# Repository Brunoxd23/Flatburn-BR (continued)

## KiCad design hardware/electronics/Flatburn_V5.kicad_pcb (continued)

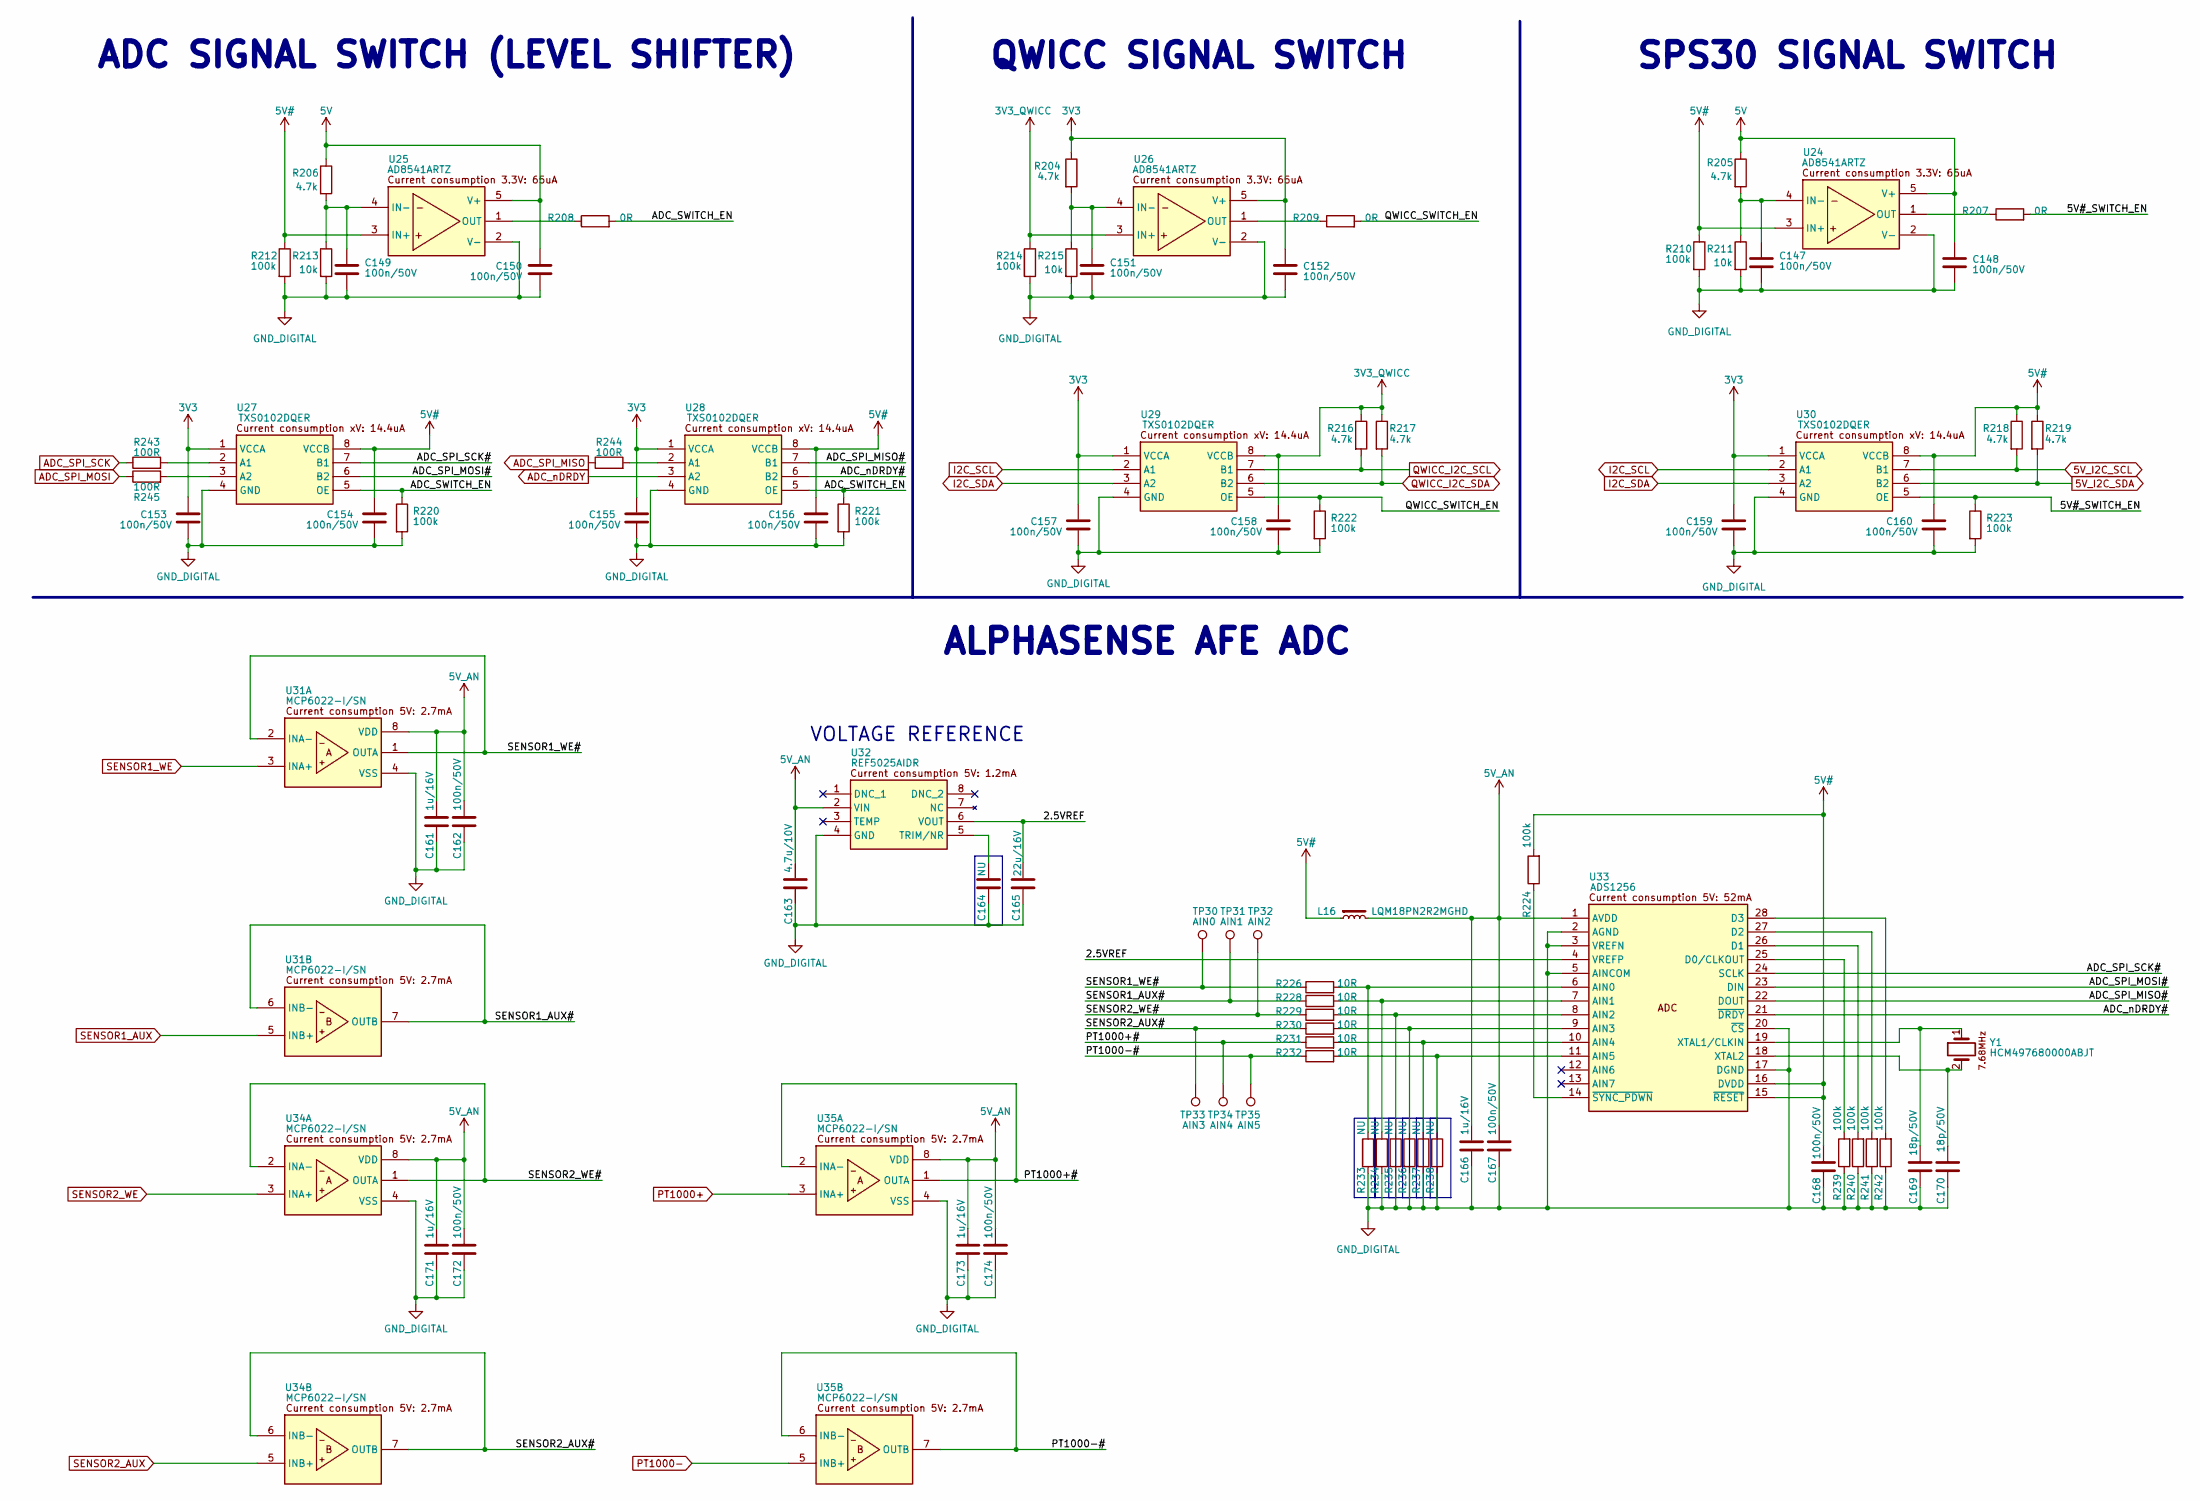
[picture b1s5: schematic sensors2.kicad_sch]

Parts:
C147, C148, C149, C150, C151, C152, C153, C154, C155, C156, C157, C158, C159, C160, C162, C167, C168, C172, C174: 100n/50V; C_0402_1005Metric
C161, C166, C171, C173: 1u/16V; C_0402_1005Metric; MPN GRM155C71C105KE11D
C163: 4.7u/10V; C_0603_1608Metric
C164: NU; C_0603_1608Metric; MPN CL10B105KA8NNNC
C165: 22u/16V; C_0603_1608Metric; MPN KGM15CR51C226MT
C169, C170: 18p/50V; C_0603_1608Metric; MPN C0603C180J5GAC7411
L16: LQM18PN2R2MGHD; L_0603_1608Metric; MPN LQM18PN2R2MGHD
R204, R205, R206, R216, R217, R218, R219: 4.7k; R_0402_1005Metric
R207, R208, R209: 0R; R_0402_1005Metric; MPN RCS04020000Z0ED
R210, R212, R214, R220, R221, R222, R223, R224, R239, R240, R241, R242: 100k; R_0402_1005Metric
R211, R213, R215: 10k; R_0402_1005Metric
R226, R228, R229, R230, R231, R232: 10R; R_0402_1005Metric; MPN RE0402DRE0710RL
R233, R234, R235, R236, R237, R238: NU; R_0402_1005Metric
R243, R244, R245: 100R; R_0402_1005Metric
TP30: AIN0; TestPoint_Pad_D1.0mm
TP31: AIN1; TestPoint_Pad_D1.0mm
TP32: AIN2; TestPoint_Pad_D1.0mm
TP33: AIN3; TestPoint_Pad_D1.0mm
TP34: AIN4; TestPoint_Pad_D1.0mm
TP35: AIN5; TestPoint_Pad_D1.0mm
U24, U25, U26: AD8541ARTZ; SOT-23-5; MPN TXS0102DQER
U27, U28, U29, U30: TXS0102DQER; SON35P100X140X40-8N; MPN TXS0102DQER
U31, U34, U35: MCP6022-I/SN; SOIC127P600X175-8N; MPN MCP6022-I/SN
U32: REF5025AIDR; SOIC127P600X175-8N; MPN REF5025AIDR
U33: ADS1256; DB28-M; MPN ADS1256IDBR
Y1: HCM497680000ABJT; MPN HCM497680000ABJT

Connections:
3V3: C152.1, C153.1, C155.1, C157.1, C159.1, R204.1, U26.5 (V+), U27.1 (VCCA), U28.1 (VCCA), U29.1 (VCCA), U30.1 (VCCA); also elsewhere on the board
3V3_QWICC: C158.1, R214.1, R216.1, R217.1, U26.3 (IN+), U29.8 (VCCB); also elsewhere on the board
5V: C148.1, C150.1, R205.1, R206.1, U24.5 (V+), U25.5 (V+); also elsewhere on the board
5V#: C154.1, C156.1, C160.1, C168.1, L16.2, R210.1, R212.1, R218.1, R219.1, R224.2, U24.3 (IN+), U25.3 (IN+), U27.8 (VCCB), U28.8 (VCCB), U30.8 (VCCB), U33.15 (~RESET), U33.16 (DVDD); also elsewhere on the board
5V_AN: C161.1, C162.1, C163.1, C166.1, C167.1, C171.1, C172.1, C173.1, C174.1, L16.1, U31.8 (VDD), U32.2 (VIN), U33.1 (AVDD), U34.8 (VDD), U35.8 (VDD)
5V_I2C_SCL: R218.2, U30.7 (B1); also elsewhere on the board
5V_I2C_SDA: R219.2, U30.6 (B2); also elsewhere on the board
/08 - SENSORS 2/2.5VREF: C165.1, U32.6 (VOUT), U33.4 (VREFP)
/08 - SENSORS 2/5V#_SWITCH_EN: R207.2, R223.1, U30.5 (OE)
/08 - SENSORS 2/ADC_SPI_MISO#: U28.7 (B1), U33.22 (DOUT)
/08 - SENSORS 2/ADC_SPI_MOSI#: U27.6 (B2), U33.23 (DIN)
/08 - SENSORS 2/ADC_SPI_SCK#: U27.7 (B1), U33.24 (SCLK)
/08 - SENSORS 2/ADC_SWITCH_EN: R208.2, R220.1, R221.1, U27.5 (OE), U28.5 (OE)
/08 - SENSORS 2/ADC_nDRDY#: U28.6 (B2), U33.21 (~DRDY)
/08 - SENSORS 2/PT1000+#: R231.1, TP34.1, U35.1 (OUTA), U35.2 (INA-)
/08 - SENSORS 2/PT1000-#: R232.1, TP35.1, U35.6 (INB-), U35.7 (OUTB)
/08 - SENSORS 2/QWICC_SWITCH_EN: R209.2, R222.1, U29.5 (OE)
/08 - SENSORS 2/SENSOR1_AUX#: R228.1, TP31.1, U31.6 (INB-), U31.7 (OUTB)
/08 - SENSORS 2/SENSOR1_WE#: R226.1, TP30.1, U31.1 (OUTA), U31.2 (INA-)
/08 - SENSORS 2/SENSOR2_AUX#: R230.1, TP33.1, U34.6 (INB-), U34.7 (OUTB)
/08 - SENSORS 2/SENSOR2_WE#: R229.1, TP32.1, U34.1 (OUTA), U34.2 (INA-)
ADC_SPI_MISO: R244.1; also elsewhere on the board
ADC_SPI_MOSI: R245.1; also elsewhere on the board
ADC_SPI_SCK: R243.1; also elsewhere on the board
ADC_nDRDY: U28.3 (A2); also elsewhere on the board
GND_DIGITAL: C147.2, C148.2, C149.2, C150.2, C151.2, C152.2, C153.2, C154.2, C155.2, C156.2, C157.2, C158.2, C159.2, C160.2, C161.2, C162.2, C163.2, C164.2, C165.2, C166.2, C167.2, C168.2, C169.2, C170.2, C171.2, C172.2, C173.2, C174.2, R210.2, R211.2, R212.2, R213.2, R214.2, R215.2, R220.2, R221.2, R222.2, R223.2, R233.2, R234.2, R235.2, R236.2, R237.2, R238.2, R239.1, R240.1, R241.1, R242.1, U24.2 (V-), U25.2 (V-), U26.2 (V-), U27.4 (GND), U28.4 (GND), U29.4 (GND), U30.4 (GND), U31.4 (VSS), U32.4 (GND), U33.2 (AGND), U33.3 (VREFN), U33.5 (AINCOM), U33.17 (DGND), U33.20 (~CS), U34.4 (VSS), U35.4 (VSS); also elsewhere on the board
I2C_SCL: U29.2 (A1), U30.2 (A1); also elsewhere on the board
I2C_SDA: U29.3 (A2), U30.3 (A2); also elsewhere on the board
unnamed: C147.1, R205.2, R211.1, U24.4 (IN-)
unnamed: R207.1, U24.1 (OUT)
unnamed: C149.1, R206.2, R213.1, U25.4 (IN-)
unnamed: R208.1, U25.1 (OUT)
unnamed: C151.1, R204.2, R215.1, U26.4 (IN-)
unnamed: R209.1, U26.1 (OUT)
unnamed: R243.2, U27.2 (A1)
unnamed: R245.2, U27.3 (A2)
unnamed: R244.2, U28.2 (A1)
unnamed: C164.1, U32.5 (TRIM/NR)
unnamed: R226.2, R233.1, U33.6 (AIN0)
unnamed: R228.2, R234.1, U33.7 (AIN1)
unnamed: R229.2, R235.1, U33.8 (AIN2)
unnamed: R230.2, R236.1, U33.9 (AIN3)
unnamed: R231.2, R237.1, U33.10 (AIN4)
unnamed: R232.2, R238.1, U33.11 (AIN5)
unnamed: R239.2, U33.25 (D0/CLKOUT)
unnamed: R240.2, U33.26 (D1)
unnamed: R241.2, U33.27 (D2)
unnamed: R242.2, U33.28 (D3)
unnamed: C169.1, U33.19 (XTAL1/CLKIN), Y1.1
unnamed: C170.1, U33.18 (XTAL2), Y1.2
unnamed: R224.1, U33.14 (~SYNC_PDWN)
PT1000+: U35.3 (INA+); also elsewhere on the board
PT1000-: U35.5 (INB+); also elsewhere on the board
QWICC_I2C_SCL: R216.2, U29.7 (B1); also elsewhere on the board
QWICC_I2C_SDA: R217.2, U29.6 (B2); also elsewhere on the board
SENSOR1_AUX: U31.5 (INB+); also elsewhere on the board
SENSOR1_WE: U31.3 (INA+); also elsewhere on the board
SENSOR2_AUX: U34.5 (INB+); also elsewhere on the board
SENSOR2_WE: U34.3 (INA+); also elsewhere on the board

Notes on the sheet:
QWICC SIGNAL SWITCH
VOLTAGE REFERENCE
SPS30 SIGNAL SWITCH
ALPHASENSE AFE ADC
ADC SIGNAL SWITCH (LEVEL SHIFTER)

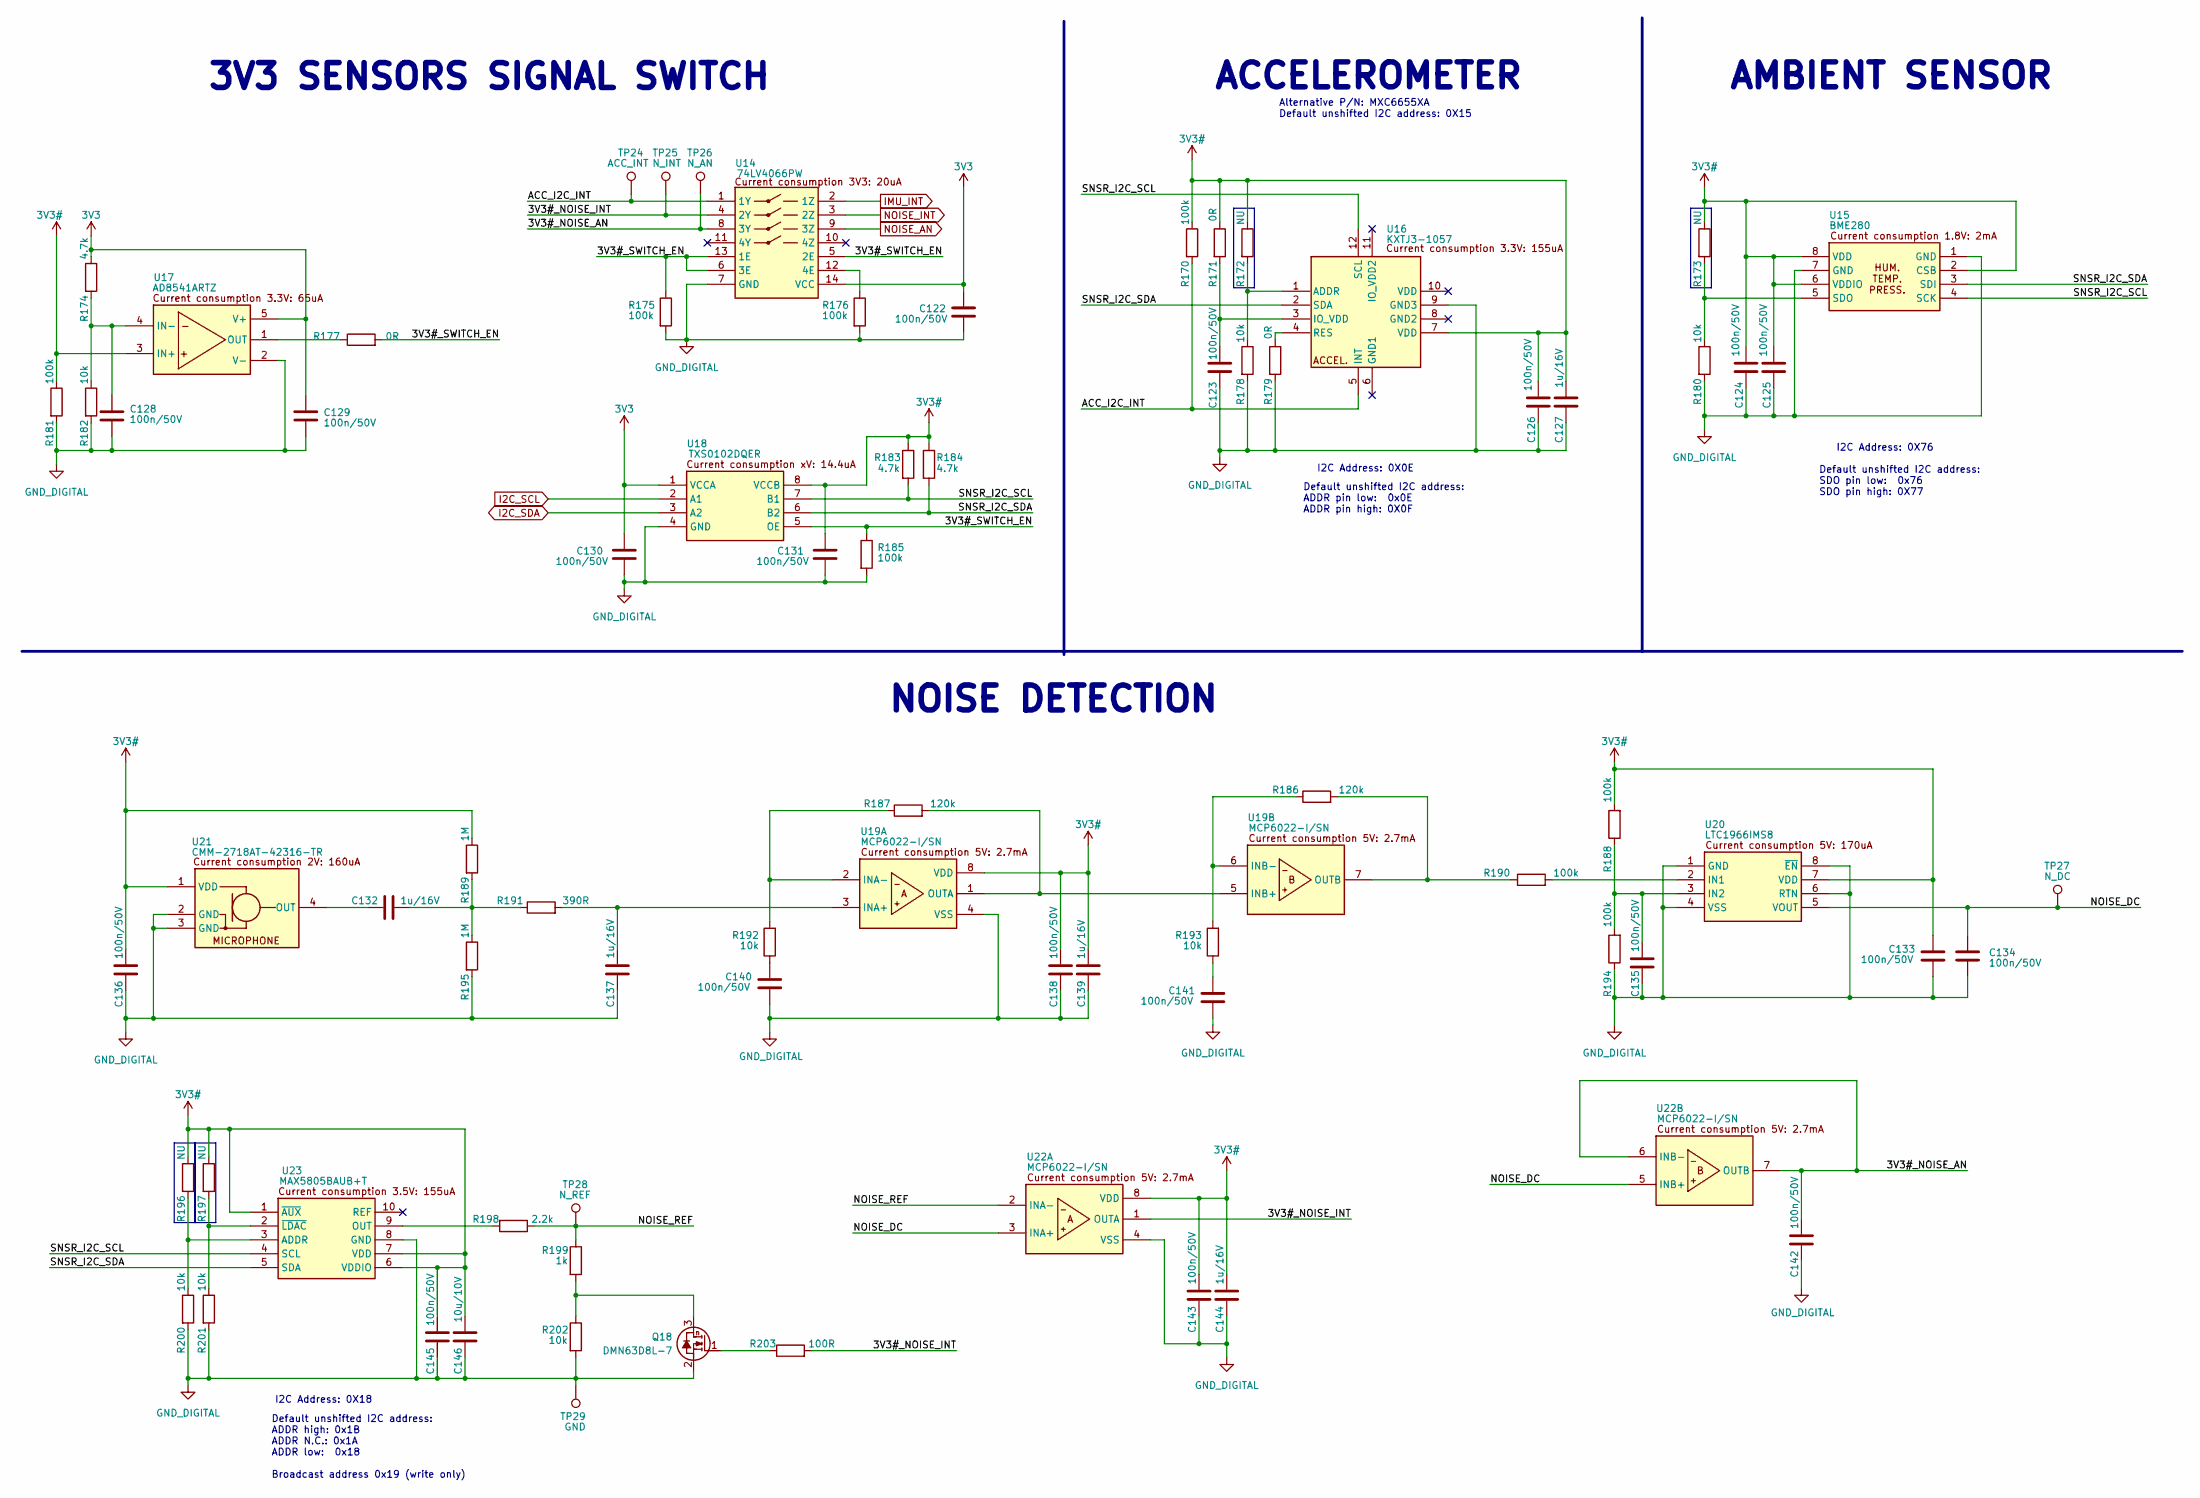
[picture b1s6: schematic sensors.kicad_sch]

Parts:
C122, C123, C124, C125, C126, C128, C129, C130, C131, C133, C134, C135, C136, C138, C140, C141, C142, C143, C145: 100n/50V; C_0402_1005Metric
C127, C132, C137, C139, C144: 1u/16V; C_0402_1005Metric; MPN GRM155C71C105KE11D
C146: 10u/10V; C_0603_1608Metric
Q18: DMN63D8L-7; SOT-23; MPN DMN63D8L-7
R170, R175, R176, R181, R185, R188, R190, R194: 100k; R_0402_1005Metric
R171, R177, R179: 0R; R_0402_1005Metric; MPN RCS04020000Z0ED
R172, R173, R196, R197: NU; R_0402_1005Metric
R174, R183, R184: 4.7k; R_0402_1005Metric
R178, R180, R182, R192, R193, R200, R201, R202: 10k; R_0402_1005Metric
R186, R187: 120k; R_0402_1005Metric; MPN CRCW0402120KFKED
R189, R195: 1M; R_0402_1005Metric
R191: 390R; R_0603_1608Metric
R198: 2.2k; R_0402_1005Metric
R199: 1k; R_0402_1005Metric
R203: 100R; R_0402_1005Metric
TP24: ACC_INT; TestPoint_Pad_D1.0mm
TP25: N_INT; TestPoint_Pad_D1.0mm
TP26: N_AN; TestPoint_Pad_D1.0mm
TP27: N_DC; TestPoint_Pad_D1.0mm
TP28: N_REF; TestPoint_Pad_D1.0mm
TP29: GND; TestPoint_Pad_D1.0mm
U14: 74LV4066PW; SOP65P640X110-14N; MPN 74LV4066PW,118
U15: BME280; PSON65P250X250X100-8N; MPN BME280
U16: KXTJ3-1057; LGA12_2X2X0.9_KNX-M; MPN KXTJ3-1057
U17: AD8541ARTZ; SOT-23-5; MPN TXS0102DQER
U18: TXS0102DQER; SON35P100X140X40-8N; MPN TXS0102DQER
U19, U22: MCP6022-I/SN; SOIC127P600X175-8N; MPN MCP6022-I/SN
U20: LTC1966IMS8; SOP65P490X110-8N; MPN LTC1966IMS8#PBF
U21: CMM-2718AT-42316-TR; CMM2718AT42316TR; MPN CMM-2718AT-42316-TR
U23: MAX5805BAUB+T; SOP50P490X110-10N; MPN MAX5805BAUB+T

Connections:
3V3: C122.1, C129.1, C130.1, R174.1, U14.14 (VCC), U17.5 (V+), U18.1 (VCCA); also elsewhere on the board
3V3#: C124.1, C125.1, C126.1, C127.1, C131.1, C133.1, C136.1, C138.1, C139.1, C143.1, C144.1, C145.1, C146.1, R170.1, R171.1, R172.1, R173.1, R181.1, R183.1, R184.1, R188.2, R189.1, R196.1, R197.1, U15.2 (CSB), U15.6 (VDDIO), U15.8 (VDD), U16.7 (VDD), U17.3 (IN+), U18.8 (VCCB), U19.8 (VDD), U20.7 (VDD), U21.1 (VDD), U22.8 (VDD), U23.1 (~AUX), U23.6 (VDDIO), U23.7 (VDD); also elsewhere on the board
/07 - SENSORS/3V3#_NOISE_AN: C142.1, TP26.1, U14.8 (3Y), U22.6 (INB-), U22.7 (OUTB)
/07 - SENSORS/3V3#_NOISE_INT: R203.2, TP25.1, U14.4 (2Y), U22.1 (OUTA)
/07 - SENSORS/3V3#_SWITCH_EN: R175.1, R177.2, R185.1, U14.5 (2E), U14.6 (3E), U14.13 (1E), U18.5 (OE)
/07 - SENSORS/ACC_I2C_INT: R170.2, TP24.1, U14.1 (1Y), U16.5 (INT)
/07 - SENSORS/NOISE_DC: C134.1, TP27.1, U20.5 (VOUT), U22.3 (INA+), U22.5 (INB+)
/07 - SENSORS/NOISE_REF: R198.1, R199.1, TP28.1, U22.2 (INA-)
/07 - SENSORS/SNSR_I2C_SCL: R183.2, U15.4 (SCK), U16.12 (SCL), U18.7 (B1), U23.4 (SCL)
/07 - SENSORS/SNSR_I2C_SDA: R184.2, U15.3 (SDI), U16.2 (SDA), U18.6 (B2), U23.5 (SDA)
GND_DIGITAL: C122.2, C123.2, C124.2, C125.2, C126.2, C127.2, C128.2, C129.2, C130.2, C131.2, C133.2, C134.2, C135.2, C136.2, C137.2, C138.2, C139.2, C140.2, C141.2, C142.2, C143.2, C144.2, C145.2, C146.2, Q18.2 (S), R175.2, R176.2, R178.2, R179.2, R180.2, R181.2, R182.2, R185.2, R194.1, R195.2, R200.2, R201.2, R202.2, TP29.1, U14.7 (GND), U15.1 (GND), U15.7 (GND), U16.9 (GND3), U17.2 (V-), U18.4 (GND), U19.4 (VSS), U20.1 (GND), U20.4 (VSS), U20.6 (RTN), U20.8 (~EN), U21.2 (GND), U21.3 (GND), U22.4 (VSS), U23.8 (GND); also elsewhere on the board
I2C_SCL: U18.2 (A1); also elsewhere on the board
I2C_SDA: U18.3 (A2); also elsewhere on the board
IMU_INT: U14.2 (1Z); also elsewhere on the board
NOISE_AN: U14.9 (3Z); also elsewhere on the board
NOISE_INT: U14.3 (2Z); also elsewhere on the board
unnamed: C132.1, R189.2, R191.1, R195.1
unnamed: C140.1, R192.1
unnamed: C141.1, R193.1
unnamed: Q18.3 (D), R199.2, R202.1
unnamed: Q18.1 (G), R203.1
unnamed: R176.1, U14.12 (4E)
unnamed: R173.2, R180.1, U15.5 (SDO)
unnamed: R172.2, R178.1, U16.1 (ADDR)
unnamed: C123.1, R171.2, U16.3 (IO_VDD)
unnamed: R179.1, U16.4 (RES)
unnamed: C128.1, R174.2, R182.1, U17.4 (IN-)
unnamed: R177.1, U17.1 (OUT)
unnamed: C137.1, R191.2, U19.3 (INA+)
unnamed: R187.1, R192.2, U19.2 (INA-)
unnamed: R187.2, U19.1 (OUTA), U19.5 (INB+)
unnamed: R186.1, R193.2, U19.6 (INB-)
unnamed: R186.2, R190.1, U19.7 (OUTB)
unnamed: R190.2, U20.2 (IN1)
unnamed: C135.1, R188.1, R194.2, U20.3 (IN2)
unnamed: C132.2, U21.4 (OUT)
unnamed: R196.2, R200.1, U23.3 (ADDR)
unnamed: R198.2, U23.9 (OUT)
unnamed: R197.2, R201.1, U23.2 (~LDAC)

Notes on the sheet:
3V3 SENSORS SIGNAL SWITCH
I2C Address: 0X76
ACCELEROMETER
Default unshifted I2C address: ADDR pin low: 0x0E ADDR pin high: 0X0F
AMBIENT SENSOR
Alternative P/N: MXC6655XA Default unshifted I2C address: 0X15
I2C Address: 0X18
I2C Address: 0X0E
NOISE DETECTION
Default unshifted I2C address: ADDR high: 0x1B ADDR N.C.: 0x1A ADDR low: 0x18 Broadcast address 0x19 (write only)
Default unshifted I2C address: SDO pin low: 0x76 SDO pin high: 0X77

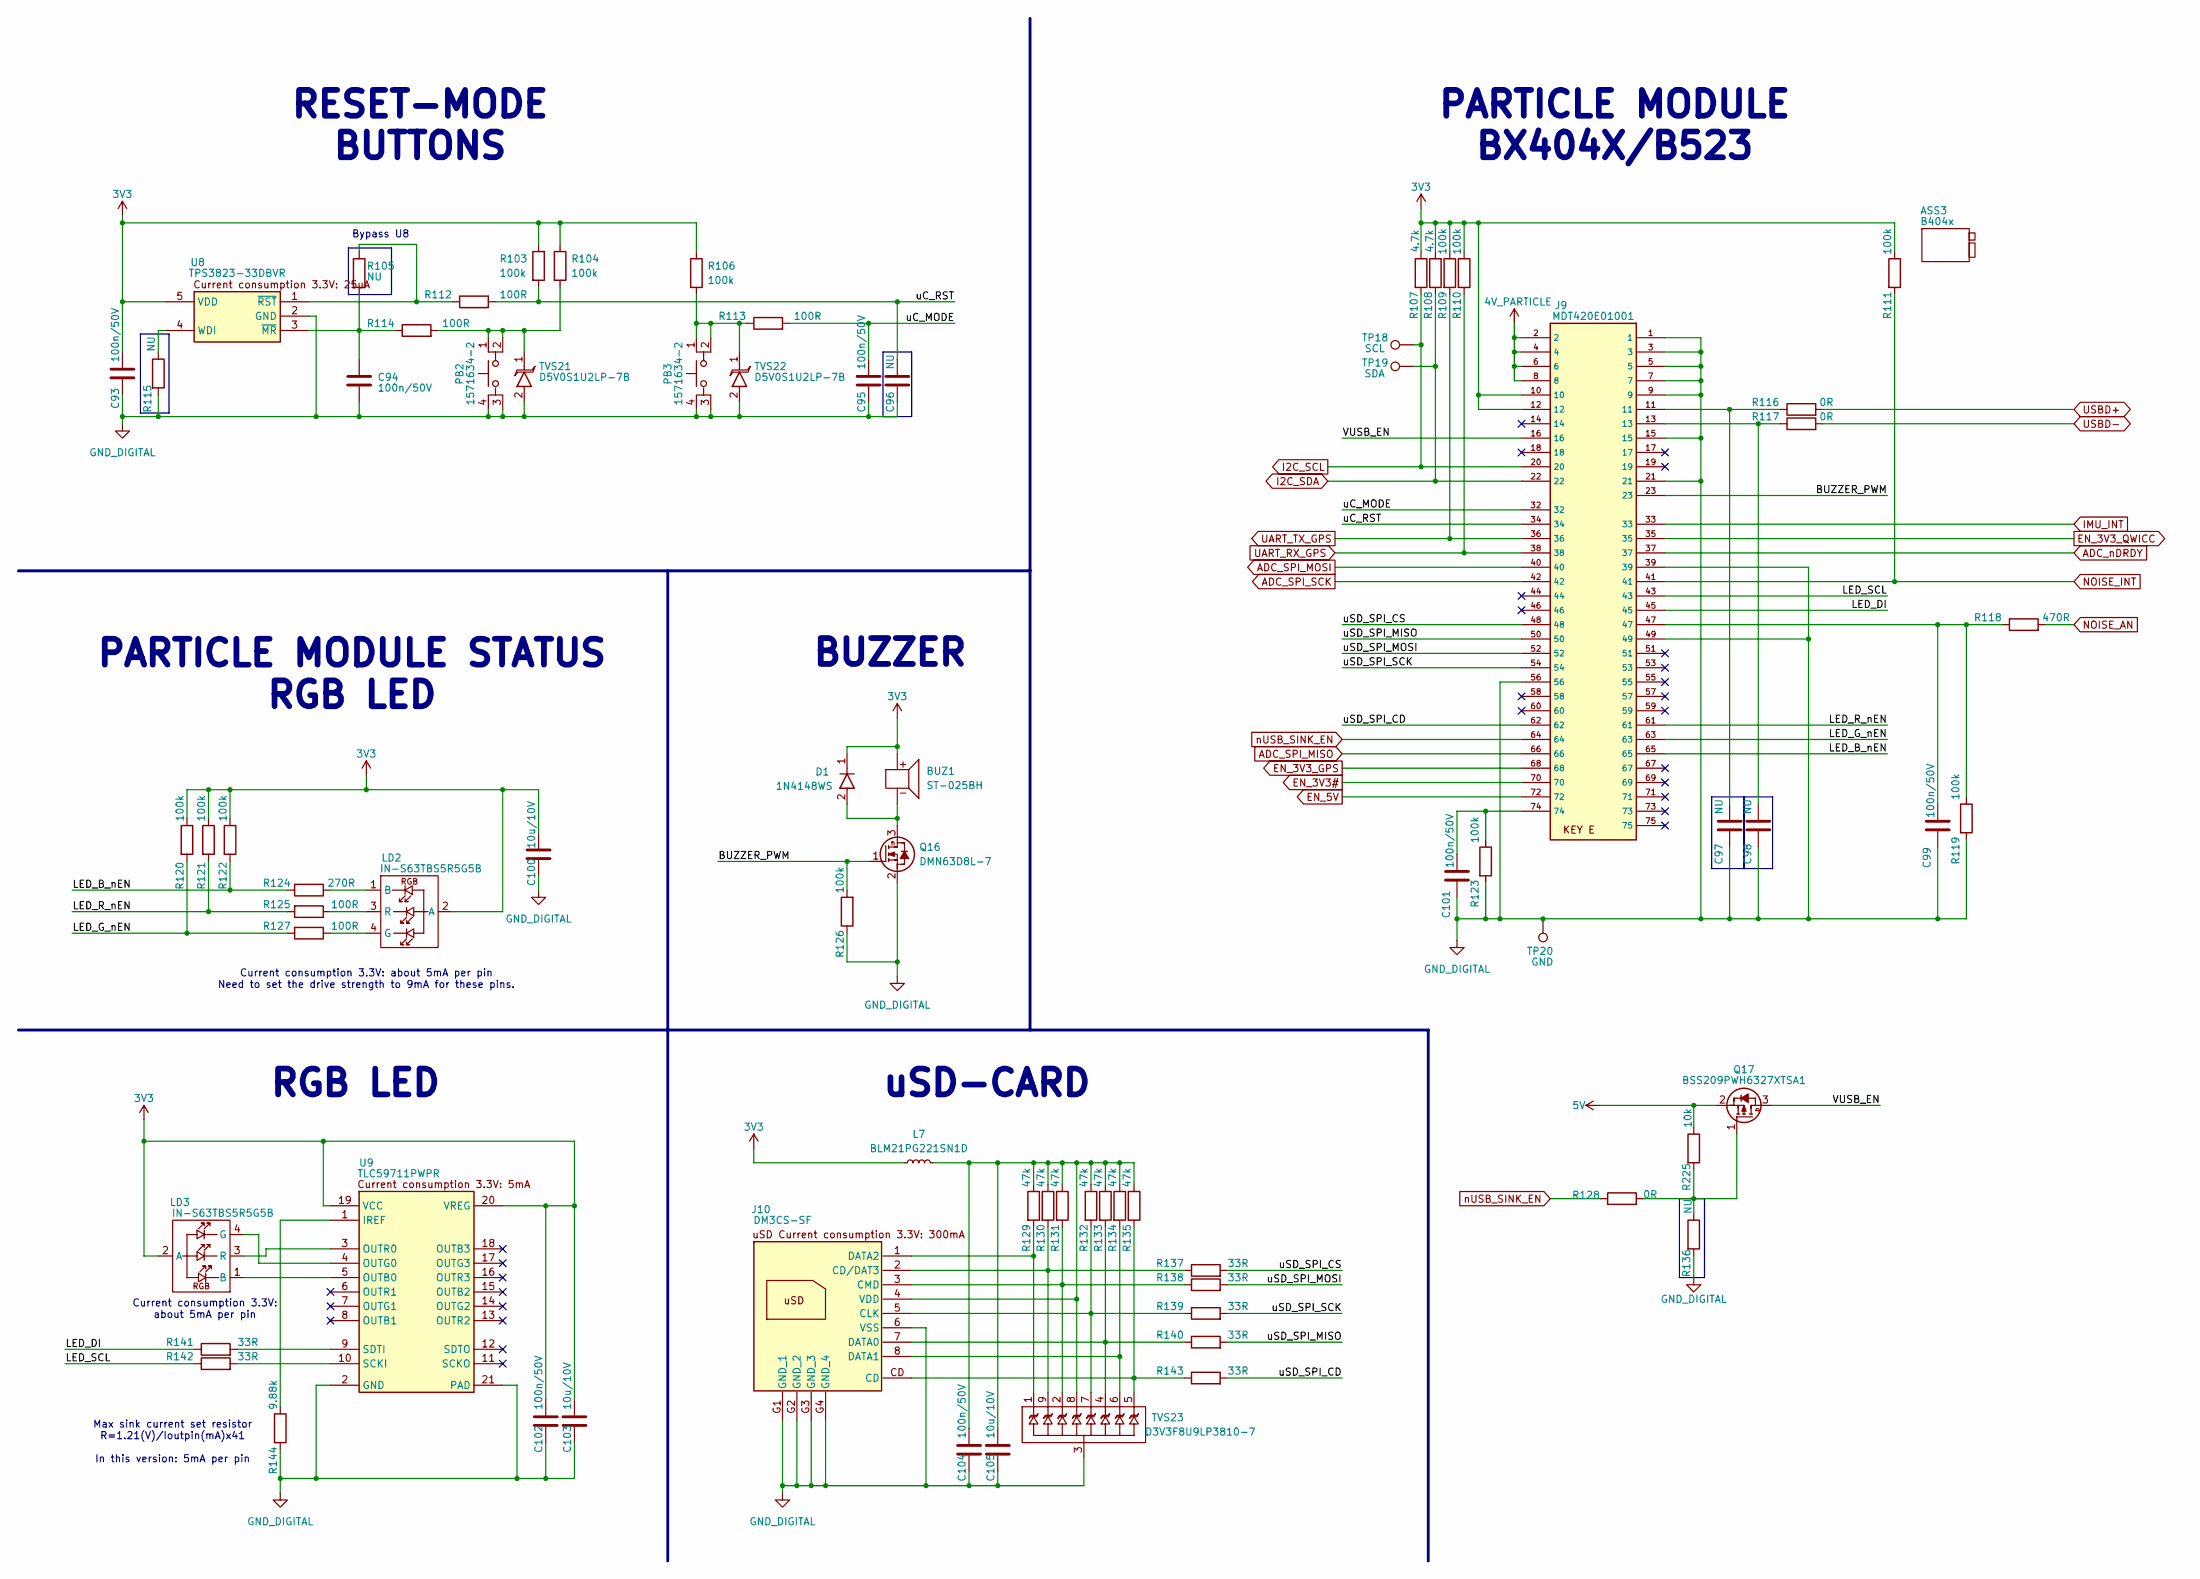
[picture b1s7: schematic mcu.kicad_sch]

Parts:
ASS3: B404x; PARTICLE B404X-B523; MPN B404x
BUZ1: ST-025BH; ST-025BH_SOB; MPN ST-025BH
C93, C94, C95, C99, C101, C102, C104: 100n/50V; C_0402_1005Metric
C96, C97, C98: NU; C_0402_1005Metric
C100, C103, C105: 10u/10V; C_0603_1608Metric
D1: 1N4148WS; D_SOD-323F; MPN 1N4148WS
J9: MDT420E01001; MPN MDT420E01001
J10: DM3CS-SF; DM3CSSF; MPN DM3CS-SF
L7: BLM21PG221SN1D; L_0805_2012Metric; MPN BLM21PG221SN1D
LD2, LD3: IN-S63TBS5R5G5B; INS63TBS5R5G5B; MPN IN-S63TBS5R5G5B
PB2, PB3: 1571634-2; 15716342; MPN 1571634-2
Q16: DMN63D8L-7; SOT-23; MPN DMN63D8L-7
Q17: BSS209PWH6327XTSA1; SOT-323_SC-70; MPN BSS209PWH6327XTSA1
R103, R104, R106, R109, R110, R111, R119, R120, R121, R122, R123, R126: 100k; R_0402_1005Metric
R105, R136: NU; R_0402_1005Metric; MPN RCS04020000Z0ED
R107, R108: 4.7k; R_0402_1005Metric
R112, R113, R114, R125, R127: 100R; R_0402_1005Metric
R115: NU; R_0402_1005Metric
R116, R117: 0R; R_0402_1005Metric; MPN MCS04020Z0000ZE000
R118: 470R; R_0402_1005Metric
R124: 270R; R_0402_1005Metric; MPN RC0402FR-07270RL
R128: 0R; R_0402_1005Metric; MPN RCS04020000Z0ED
R129, R130, R131, R132, R133, R134, R135: 47k; R_0402_1005Metric
R137, R138, R139, R140, R141, R142, R143: 33R; R_0402_1005Metric
R144: 9.88k; R_0402_1005Metric; MPN RT0402DRD079K88L
R225: 10k; R_0402_1005Metric
TP18: SCL; TestPoint_Pad_D1.0mm
TP19: SDA; TestPoint_Pad_D1.0mm
TP20: GND; TestPoint_Pad_D1.0mm
TVS21, TVS22: D5V0S1U2LP-7B; D5V0S1U2LP7B; MPN M-621-D5V0S1U2LP-7B
TVS23: D3V3F8U9LP3810-7; Diodes_UDFN3810-9_TYPE_B; MPN D3V3F8U9LP3810-7
U8: TPS3823-33DBVR; SOT-23-5; MPN TPS3823-33DBVR
U9: TLC59711PWPR; SOP65P640X120-21N; MPN TLC59711PWPR

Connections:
3V3: BUZ1.2 (+), C93.1, C100.1, C102.1, C103.1, D1.1, J9.10, J9.12, L7.2, LD2.2 (A), LD3.2 (A), R103.1, R104.1, R106.1, R107.1, R108.1, R109.1, R110.1, R111.1, R120.1, R121.1, R122.1, U8.5 (VDD), U9.19 (VCC), U9.20 (VREG); also elsewhere on the board
4V_PARTICLE: J9.2, J9.4, J9.6, J9.8; also elsewhere on the board
5V: Q17.2 (S), R225.1; also elsewhere on the board
/05 - MCU/BUZZER_PWM: J9.23, Q16.1 (G), R126.2
/05 - MCU/LED_B_nEN: J9.65, R122.2, R124.2
/05 - MCU/LED_DI: J9.45, R141.1
/05 - MCU/LED_G_nEN: J9.63, R120.2, R127.2
/05 - MCU/LED_R_nEN: J9.61, R121.2, R125.2
/05 - MCU/LED_SCL: J9.43, R142.1
/05 - MCU/VUSB_EN: J9.16, Q17.3 (D)
/05 - MCU/uC_MODE: C95.1, J9.32, R113.2
/05 - MCU/uC_RST: C96.1, J9.34, R103.2, R112.2
/05 - MCU/uSD_SPI_CD: J9.62, R143.2
/05 - MCU/uSD_SPI_CS: J9.48, R137.2
/05 - MCU/uSD_SPI_MISO: J9.50, R140.2
/05 - MCU/uSD_SPI_MOSI: J9.52, R138.2
/05 - MCU/uSD_SPI_SCK: J9.54, R139.2
ADC_SPI_MISO: J9.66; also elsewhere on the board
ADC_SPI_MOSI: J9.40; also elsewhere on the board
ADC_SPI_SCK: J9.42; also elsewhere on the board
ADC_nDRDY: J9.37; also elsewhere on the board
EN_3V3#: J9.70; also elsewhere on the board
EN_3V3_GPS: J9.68; also elsewhere on the board
EN_3V3_QWICC: J9.35; also elsewhere on the board
EN_5V: J9.72; also elsewhere on the board
GND_DIGITAL: C93.2, C94.2, C95.2, C96.2, C97.2, C98.2, C99.2, C100.2, C101.2, C102.2, C103.2, C104.2, C105.2, J9.1, J9.3, J9.5, J9.7, J9.9, J9.15, J9.21, J9.39, J9.49, J9.56, J10.6 (VSS), J10.G1 (GND_1), J10.G2 (GND_2), J10.G3 (GND_3), J10.G4 (GND_4), PB2.3, PB2.4, PB3.3, PB3.4, Q16.2 (S), R115.2, R119.2, R123.2, R126.1, R136.2, R144.2, TP20.1, TVS21.2, TVS22.2, TVS23.3, U8.2 (GND), U9.2 (GND), U9.21 (PAD); also elsewhere on the board
I2C_SCL: J9.20, R107.2, TP18.1; also elsewhere on the board
I2C_SDA: J9.22, R108.2, TP19.1; also elsewhere on the board
IMU_INT: J9.33; also elsewhere on the board
NOISE_AN: R118.2; also elsewhere on the board
NOISE_INT: J9.41, R111.2; also elsewhere on the board
unnamed: BUZ1.3 (-), D1.2, Q16.3 (D)
unnamed: C97.1, J9.11, R116.1
unnamed: C98.1, J9.13, R117.1
unnamed: C99.1, J9.47, R118.1, R119.1
unnamed: C101.1, J9.74, R123.1
unnamed: J10.2 (CD/DAT3), R130.2, R137.1, TVS23.9
unnamed: J10.5 (CLK), R132.2, R139.1, TVS23.7
unnamed: J10.3 (CMD), R131.2, R138.1, TVS23.2
unnamed: J10.7 (DATA0), R133.2, R140.1, TVS23.4
unnamed: J10.8 (DATA1), R134.2, TVS23.6
unnamed: J10.1 (DATA2), R129.2, TVS23.1
unnamed: J10.CD, R135.2, R143.1, TVS23.5
unnamed: C104.1, C105.1, J10.4 (VDD), L7.1, R129.1, R130.1, R131.1, R132.1, R133.1, R134.1, R135.1, TVS23.8
unnamed: LD2.1 (B), R124.1
unnamed: LD2.4 (G), R127.1
unnamed: LD2.3 (R), R125.1
unnamed: LD3.1 (B), U9.5 (OUTB0)
unnamed: LD3.4 (G), U9.4 (OUTG0)
unnamed: LD3.3 (R), U9.3 (OUTR0)
unnamed: PB2.1, PB2.2, R104.2, R114.2, TVS21.1
unnamed: PB3.1, PB3.2, R106.2, R113.1, TVS22.1
unnamed: Q17.1 (G), R128.2, R136.1, R225.2
unnamed: R115.1, U8.4 (WDI)
unnamed: C94.1, R105.2, R114.1, U8.3 (~MR)
unnamed: R105.1, R112.1, U8.1 (~RST)
unnamed: R144.1, U9.1 (IREF)
unnamed: R142.2, U9.10 (SCKI)
unnamed: R141.2, U9.9 (SDTI)
UART_RX_GPS: J9.38, R110.2; also elsewhere on the board
UART_TX_GPS: J9.36, R109.2; also elsewhere on the board
USBD+: R116.2; also elsewhere on the board
USBD-: R117.2; also elsewhere on the board
nUSB_SINK_EN: J9.64, R128.1; also elsewhere on the board

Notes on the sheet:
Current consumption 3.3V: about 5mA per pin Need to set the drive strength to 9mA for these pins.
BUZZER
uSD-CARD
Bypass U8
Current consumption 3.3V: about 5mA per pin
RESET-MODE BUTTONS
PARTICLE MODULE STATUS RGB LED
RGB LED
Max sink current set resistor R=1.21(V)/Ioutpin(mA)x41 In this version: 5mA per pin
PARTICLE MODULE BX404X/B523
